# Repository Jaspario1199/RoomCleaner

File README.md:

# RoomCleaner 🧺🤖

An autonomous robot that scans your room, spots dirty laundry on the floor,
picks it up, and drops it in the hamper — using four winch motors in the
ceiling corners and a downward-facing gripper on cables.

> **▶ Interactive showcase:** [`showcase/index.html`](showcase/) — a live,
> self-contained portfolio page (browser simulation + engineering analysis +
> CAD). Open it in a browser or host it free on GitHub Pages.

> **Status:** Phase 0 complete + Phase 1 scaffolded. The kinematics, fan-aware
> motion planning, auto rest-pose, and the full scan→grab→deliver loop run today
> with **zero hardware**; a real open-vocabulary laundry detector runs on a
> webcam. You only need to fill in your room dimensions and ceiling-fan location.

---

## The idea in one picture

The machine is a **Cable-Driven Parallel Robot (CDPR)** — the same mechanism
that flies the "SkyCam" over a football stadium. Four motorized winches sit in
the ceiling corners; each pays out or reels in a cable. Where the cables meet is
the end-effector (the "claw"). Control the four cable lengths and you control the
claw's position anywhere in the room.

**Why a cable robot instead of arms or a rolling vacuum?**
- It reaches the *whole floor* from above — no bumping into furniture.
- The heavy motors stay bolted to the ceiling; only a light claw moves.
- The math (below) is clean and the parts are cheap.

The trade-off is the reachable area shrinks near the walls (cables can't pull the
claw sideways into a corner). Here's the safe workspace at a low height — green is
reachable, pink is not:

That pink border is a real design constraint: **laundry pushed right against a
wall is a hard case** we'll have to handle (e.g. a longer-reach end-effector, or
just accepting a small dead-zone).

### The ceiling fan is a hard no-go zone
If you have a ceiling fan, the robot's cables must **never** touch it. RoomCleaner
models the fan as a vertical keep-out cylinder and geometrically checks *every
cable* against it — a point is only reachable if all four cables clear the fan and
the claw stays out of it. The claw also **cruises below the fan** and **parks at
an auto-computed rest pose** out of the way between jobs. You just enter the fan's
center, blade radius, and how far it hangs down; the math does the rest. Good
news from the workspace map: laundry *under* the fan is still reachable, because
when the claw drops low the cables splay out to the corners and clear the blades.

---

## Quick start

```bash
pip install -r requirements.txt
python -m scripts.demo_sim       # 3D animation of a full cleaning run
python -m scripts.sim_tension_map  # heatmap: where the motors strain hardest
python -m scripts.sim_pickup_run   # per-pickup height / cable length / tension plots
python -m scripts.sim_payload_sweep         # max liftable weight, anywhere in the room
python -m scripts.sim_calibration_sensitivity # how precisely to measure your ceiling
python -m scripts.sim_workspace_volume      # 3D render of the reachable volume
python -m pytest                 # run the kinematics/geometry/vision tests

# Phase 1 — real laundry detection on a webcam (heavier deps):
pip install -r requirements-vision.txt
python -m scripts.detect_webcam                    # detect + print floor coordinates
python -m scripts.detect_and_plan --image floor.jpg  # full pipeline: detect -> localize -> PLAN
```

### The console (operator dashboard + live perception, one app)

A local single-page web app for watching and driving the robot from a browser:

```bash
pip install -r requirements-app.txt        # just Flask; core deps cover the rest
python -m roomcleaner.app --sim            # http://127.0.0.1:8000
# or:  python quickstart.py --app          # installs + launches in one step
python -m roomcleaner.app --live --camera 1  # real camera feed + detections
python -m roomcleaner.app --live --demo      # no camera: simulated laundry,
                                             # real detection→plan pipeline
```

It shows a live feed (MJPEG) with detection boxes and a sensitivity slider,
a detected-items panel with floor coordinates, status cards (phase, claw
position, items picked, claw link/battery), per-cable tension bars checked
against the 0.5–40 N motor band, a **Robot & plan** panel (nearest-first
pickup order + per-target cable lengths A–D + max tension + reachability), a
**3-D room view** with a Live view / Animate plan toggle, a scrolling
operations log, and operator controls: Start / Pause / Resume / STOP, Home,
Park, Grip/Release, a 0.1 m jog pad (workspace-clamped, fan keep-out
enforced), and a settings drawer for room/fan/hamper geometry. `--live` runs
the real camera through the validated capture+inference threads and wires the
serial winches + WiFi gripper only if they are reachable (otherwise
camera-only, motion disabled — bench-validate motion first). Details:
[`docs/APP.md`](docs/APP.md). The software STOP is not a safety device — the
physical kill switch remains the power strip.

`detect_and_plan` is the end-to-end brain: it takes a top-down photo (or
`--webcam 0`), detects the laundry, maps each item to a floor coordinate, runs
the real pickup planner, and saves an annotated image + a 3D scene. Test it on a
phone photo today — no camera or robot required.

The sim demo scatters fake laundry, then runs the real control loop to clear the
floor and animates the result. **Before anything else, open
`roomcleaner/config.py` and fill in the two "EDIT ME" blocks** — your room
dimensions and your ceiling-fan location/size.

---

## How it works (the four subsystems)

### 1. Kinematics — `roomcleaner/kinematics.py`
The core math, and it's simpler than it looks:

- **Inverse kinematics** ("put the claw *here* → how long is each cable?") is just
  the straight-line distance from each ceiling anchor to the target point.
- **Forward kinematics** ("cables are *these* lengths → where's the claw?") is a
  least-squares fit, because real cable measurements are never perfectly
  consistent.
- **Statics** ("can four *pull-only* cables actually hold the claw here without
  exceeding the motor's force limit?") defines the usable workspace. Cables can
  pull but never push, so this is the constraint that carves out those pink edges.

### 2. Perception — `roomcleaner/perception/`
Finds laundry and locates it on the floor. A `SimulatedDetector` invents laundry
for the sim, and `YoloWorldDetector` does the real thing on a webcam using an
**open-vocabulary** model (detects "sock", "towel", … from *words*, no training).
Both share the **exact same interface**, so the control loop never changes.
`localization.py` maps a camera pixel to a floor `(x, y)` — zero-calibration for a
straight-down ceiling camera, or a precise 4-point homography for a tilted one.
See **[docs/VISION.md](docs/VISION.md)**.

### 3. Motion planning — `roomcleaner/control/trajectory.py`
Turns "go to point X" into a smooth, ease-in/ease-out path. The `safe_transit`
helper always travels *up → across → down* so the claw never drags across the
floor or clips furniture.

### 4. Orchestration — `roomcleaner/control/state_machine.py`
The brain: an explicit state machine
(`SCAN → SELECT → APPROACH → GRAB → DELIVER → DONE`) that clears the floor one
item at a time, nearest first. Keeping it an explicit state machine (not tangled
`if`s) makes safety easy to reason about and new states easy to add.

---

## Repository layout

```
roomcleaner/
  config.py               # ROOM + FAN dimensions, motor limits, margins — the ONLY file you edit
  kinematics.py           # inverse/forward kinematics + statics/workspace + rest-pose finder
  geometry.py             # fan keep-out: exact cable-vs-cylinder intersection tests
  simulator.py            # 3D visualiser (renders to PNG/GIF, no display needed)
  perception/
    detector.py           # Detector interface + SimulatedDetector
    vision_detector.py    # real open-vocabulary laundry detector (YOLO-World)
    localization.py       # pixel → floor (x,y): overhead-linear + homography mappers
    camera.py             # webcam capture wrapper (OpenCV)
  control/
    trajectory.py         # smooth path generation
    state_machine.py      # the scan→grab→deliver brain (emits move/grip/release actions)
  hardware/
    driver.py             # positions → winch steps + serial protocol (Serial/Mock)
    gripper.py            # gripper backends: WiFiGripper (wireless claw) / Serial / Mock
    executor.py           # stream a plan to the motors + gripper
    hw_config.py          # steps/rev, microstepping, drum dia, serial port, effector IP
roomcleaner/cdpr/         # GEN-2 CONTROL SYSTEM (see docs/CONTROL_SYSTEM_V1.md)
  station_core.py         # executable spec of the winch-station firmware
  coordinator.py          # synchronized segment streams, feed-hold, leases
  calibration.py          # self-calibration estimator + identifiability + excitation
  startup.py              # DISARMED -> ... -> READY sequencer (bounded, abortable)
  homing.py               # sequential bead verification
  supervisor.py           # PAUSED/FAULT/RECOVERY_REQUIRED/PARKED, no auto-resume
  tasks.py                # SCAN -> ... -> DELIVERY_VERIFICATION
  service.py, static/     # phone setup page + API (python -m roomcleaner.cdpr.service --sim)
  sim/                    # physics world, simulated stations/network/camera/claw
firmware/
  winch_station/          # gen-2 station core (C++, conformance-tested vs Python)
  claw_s3/                # gen-2 claw node: camera frames, IMU, servo, battery
  roomcleaner_firmware/   # Arduino sketch: 4 winch steppers + homing (wired)
  effector_esp32/         # ESP32 sketch: wireless gripper servo over WiFi
scripts/
  demo_sim.py             # end-to-end simulation demo
  detect_webcam.py        # live laundry detection from a webcam
  detect_and_plan.py      # full pipeline: image/webcam → detect → localize → plan
  hardware_dryrun.py      # print the serial command stream (no Arduino needed)
tests/
  test_kinematics.py      # the math we must trust
  test_geometry.py        # fan keep-out safety tests
  test_localization.py    # pixel → floor mapping tests
docs/
  ROADMAP.md              # phase-by-phase build plan
  HARDWARE.md             # BOM (cheap Amazon parts) + gripper recommendation
  VISION.md               # perception & camera calibration guide
  ARCHITECTURE.md         # how the pieces fit + the design decisions
  RESEARCH.md             # sources behind the hardware/gripper choices
```

---

## Where this is going

See **[docs/ROADMAP.md](docs/ROADMAP.md)** for the full plan. The short version:

| Phase | What | Cost |
|------|------|------|
| **0** ✅ | Kinematics + simulator + control loop + fan safety + rest pose | Free (software) |
| **1** 🚧 | Real laundry detection & floor localization (runs on a webcam) | Free–cheap (a webcam) |
| **2** | Motion planning polish, full-path safety, sim tuning | Free |
| **3** | Hardware bring-up: motors, drivers, camera, e-stop | 💰 the build (~$250–515, see BOM) |
| **4** | The grasp — actually picking cloth off the floor | 💰 the experiment |

The two genuinely hard, risky parts are called out honestly in the docs:
**grasping deformable cloth** (Phase 4) and **safety** (a motor that can move a
payload across your ceiling can hurt someone). We de-risk everything cheap in
software first.

---

## The gripper — a tentacle hand (mechanical, no vacuum)

Grabbing crumpled cloth off a hard floor is the classic failure point. The chosen
design is a **ring of tendon-driven curling "tentacle" fingers** that descend and
curl **inward and under**, raking and wrapping the laundry toward the center — one
servo closes them all. For real, crumpled laundry this beats a rigid claw because
it gathers rather than needing something to pinch. It's fully modeled and
print-ready in **[`cad/`](cad/)** (`tentacle_finger` × 5 + `tentacle_hub` +
`effector_frame`). Full reasoning and the needle-gripper fallback are in
**[docs/HARDWARE.md](docs/HARDWARE.md)**.

## 3D-printed parts (CAD)

Everything mechanical that can be printed is provided as **parametric CadQuery
scripts** exporting genuine **STEP** + **STL** files: winch spools, motor mounts,
corner guides, the end-effector frame, and the whole tentacle gripper. Edit your
dimensions in `cad/params.py` and run `python -m cad.export_all` to regenerate.
See **[cad/README.md](cad/README.md)** for print settings and assembly. (The
load-bearing ceiling anchors stay **metal** — never printed.)

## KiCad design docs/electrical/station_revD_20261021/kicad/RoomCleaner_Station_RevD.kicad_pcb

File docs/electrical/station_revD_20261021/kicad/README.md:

# Winch station Rev D, as soldered: KiCad 7 project

One A3 schematic, a netlist, a PDF/PNG, and a no-routing PCB (ratsnest only) of the
station perfboard (5 x 7 cm, 24 columns A-X x 18 rows 01-18, 2.54 mm). Everything is
generated from `../perfboard_layout.py`, the as-soldered, net-checked design. If the
Rev D schematic (`../draw_schematic.py`, `../README.md`) and the perfboard file disagree,
the perfboard file wins (list below). Current limit: DECISIONS.md **D30** (Vref about
0.85 V, about 1.06 A), not the 1.35 A / 1.08 V of the Rev D README.

## Open it

KiCad 7.0.x: open `RoomCleaner_Station_RevD.kicad_pro`.
The schematic is `RoomCleaner_Station_RevD.kicad_sch` (A3, one sheet), the PCB
`RoomCleaner_Station_RevD.kicad_pcb`. `sym-lib-table` / `fp-lib-table` name the stock
libraries through `${KICAD7_SYMBOL_DIR}` / `${KICAD7_FOOTPRINT_DIR}` and the project
libraries `RoomCleaner.kicad_sym` / `RoomCleaner.pretty` through `${KIPRJMOD}`.
The PCB shows the connections as a ratsnest (no tracks: the copper on the real board is
bare wire and solder runs, see `../PERFBOARD_LAYOUT.md`).

| File | What |
|---|---|
| `build_kicad.py` | generator for everything below (also runs the exports, the PCB, DRC, the net check) |
| `perfboard_data.py` | the bridge to `perfboard_layout.py`: loads its tables, holds the one hole-to-pin map |
| `check_netlist.py` | compares the exported netlist (and the PCB) with the perfboard nets; prints PASS/FAIL |
| `run_erc_xvfb.py` | runs KiCad's real ERC headlessly (see ERC below) |
| `RoomCleaner_Station_RevD.kicad_pro/.kicad_sch/.kicad_pcb` | project, schematic, PCB |
| `RoomCleaner.kicad_sym`, `RoomCleaner.pretty/` | custom XIAO ESP32-C3 and DROK buck symbols + footprints |
| `sym-lib-table`, `fp-lib-table` | project library tables |
| `RoomCleaner_Station_RevD_netlist.xml` | `kicad-cli sch export netlist --format kicadxml` |
| `RoomCleaner_Station_RevD.pdf`, `..._preview.png` | `kicad-cli sch export pdf`, `pdftoppm -r 110 -png` |
| `netlist_check.txt` | output of `check_netlist.py --pcb` (PASS) |
| `RoomCleaner_Station_RevD_erc.rpt` | KiCad 7 ERC report (0 errors, 0 warnings) |
| `RoomCleaner_Station_RevD_drc.rpt`, `..._pcb_preview.png` | PCB DRC report; trimmed render of the placed board |

## Regenerate

```
cd docs/electrical/station_revD_20261021/kicad
/usr/bin/python3 build_kicad.py            # project, netlist, PDF, PNG, PCB, DRC, netlist_check.txt
/usr/bin/python3 build_kicad.py --erc      # same + real ERC through eeschema under Xvfb (about 1 min)
/usr/bin/python3 build_kicad.py --no-pcb   # schematic side only (also --no-export, --no-drc)
python3 check_netlist.py                   # netlist only, stdlib only; add --pcb with /usr/bin/python3
```

Use `/usr/bin/python3` (the one with `pcbnew`). `perfboard_layout.py` is **not imported**:
importing it runs its matplotlib code and rewrites `perfboard_layout.png/.pdf`. Instead
`perfboard_data.py` executes only its table/check section (above the `# --- drawing`
marker) and never writes anything outside this folder. Schematic, libraries and project
files are deterministic (fixed UUID namespace); the netlist XML carries a date and pcbnew
assigns fresh item UUIDs to the PCB on every run.

Where a perfboard fact had to be turned into a schematic fact, the map lives in one place,
`perfboard_data.py`: `HOLE_PIN` (hole -> connector/part pin, with the perfboard label as a
cross-check), `XIAO_PIN`, `A4988_PIN` + `A4988_GND_BY_HOLE`, and `NET_NAME`
(perfboard `12V`/`3V3`/`5V` -> the power symbols `+12V`/`+3V3`/`+5V`; `PGND` is folded into
`GND` by the perfboard file's own `NETMAP`). Every hole in `PINS` must be mapped exactly once,
and the generator checks that the XIAO / A4988 pin names match the perfboard labels. The PCB
step then places each footprint with pad 1 on its hole and checks that **every pad of every
footprint lands on the hole the map says** (worst error 0.04 mm, C1), which independently
confirms the pad numbering of the stock A4988 footprint.

## Results

* **ERC (KiCad 7.0.11): 0 errors, 0 warnings.** Note: `kicad-cli` 7.0.11 has **no**
  `sch erc` (or `pcb drc`) subcommand; both arrived in KiCad 8. The ERC was therefore run with
  the real eeschema ERC engine by driving the GUI under Xvfb (`run_erc_xvfb.py`: Inspect >
  Electrical Rules Checker > Run ERC > Save, on a temporary copy of the project and a temporary
  config dir). KiCad's only ignored test is its default-off "SPICE model issue". To show the run
  is not vacuous, the same script on a copy with the three PWR_FLAGs and one wire removed
  reports 4 errors (pin not connected, 3x power pin not driven). PWR_FLAGs: +12V and GND at J1,
  +5V at JP1's XIAO side. The stock-symbol copies embedded in the schematic match the library
  (no "symbol doesn't match library" warning).
* **Netlist: PASS** (`netlist_check.txt`): 16 nets / 55 connected pins identical, per net, to the
  perfboard; 6 pins unconnected on both sides (U1 EN, XIAO D0 D6 D7 D8 D9); 14 components.
  Mutation tests (a pin dropped from SDA, a pin moved from STEP to EN) print FAIL.
* **PCB / DRC:** 70 x 50 mm outline, hole A01 at (101.6, 76.2) mm with equal margins to the
  board edge (5.79 / 3.41 mm), all 14 footprints on their holes, 22 nets (16 + 6 `unconnected-`),
  no routing. DRC runs through `pcbnew.WriteDRCReport` (same engine as the GUI): **0 errors
  other than the 39 "unconnected items" (the ratsnest)**, 5 warnings: 3 courtyard overlaps on
  adjacent holes (JP1/D1, JP1/U3, R4/J3; the bodies do not collide, the stock 0.5 mm connector
  courtyard margins do) which the project sets to *warning* (`courtyards_overlap` in
  `.kicad_pro`), and 2 silkscreen overlaps between neighbouring outlines around JP1 / U3 (x 142-146 mm). Designators are on the
  fab layer to keep the silk readable. Footprints carry the schematic symbol UUID path so
  "Update PCB from Schematic" should match them (not exercised in the GUI).

## What is off-board

Drawn as dashed blocks next to their connectors, not as parts: **AS5600 encoder** on J5
(C17-F17: 3V3, GND, SDA, SCL), **KW12-3 NC switch** on J3 (H17 NC -> HOME, I17 COM -> GND),
the **NEMA 17 motor** on J2 (X05-X08), the **12 V supply branch** on J1 (+ its supply-end fuses
F0-F4, which are notes only) and the XIAO's USB cable. The DROK module is modeled as a 5-pin
header part (pads only; its body is not modeled).

## Disagreements Rev D schematic vs perfboard (perfboard followed)

1. Current limit: Rev D README / sheet 3 / sheet 5 say 1.35 A, Vref 1.08 V (D29). The sheet
   follows D30: **Vref 0.85 V, about 1.06 A**; 1.08 V is noted as not reachable on this carrier.
2. Encoder: sheet 3 draws AS5600 DIR -> GND and OUT open at the encoder. The perfboard J5 has
   4 pins only (3V3, GND, SDA, SCL), so those two connections are on the encoder board, not
   the perfboard.
3. Test points TP0-TP4 (sheets 1, 2, 4) are not parts on the perfboard; omitted.
4. Grounds: Rev D shows one GND. The perfboard has two A4988 GND pads (pad 7 next to VMOT =
   motor return `PGND`, pad 1 = logic) joined by wire S03-O11; after `NETMAP` that is one net,
   drawn as one `GND`.
5. Net names: Rev D sheet 4 (`+12_STATION`, `+5_BUCK`, `DIODE OUTPUT`, `XIAO_5V`, `ENABLE`,
   `HOME_NC`) are `+12V`, `5VB`, `5VD`, `+5V`, `EN`, `HOME` here.
6. Packages as built: R2/R3 stand upright (2.54 mm holes), R1/R4 lie (7.62 mm); J1 uses a
   5.08 mm terminal pitch (X01 / X03), not a 2.54 mm header.

## Known limits

* Footprints: stock footprints except the XIAO (outline approximate) and the DROK header.
  R = DIN0204 (3.6 mm) so the 2.54 mm-pitch courtyards of R1-R3 do not collide; any 1/8-1/4 W
  10k fits electrically. C1 = `CP_Radial_D6.3mm_P2.50mm` (2.50 vs 2.54 mm hole pitch, 0.04 mm
  off); the real 100 uF/50 V can may be larger. J1 uses the 5.08 mm terminal footprint instead
  of a pin header because X01-X03 are 5.08 mm apart. No 3D models for the custom footprints.
* Resistors and JP1 are symmetric; their pin 1/2 assignment is arbitrary (pin 1 = upper lead in
  the drawing, JP1 pin 1 = diode side).
* The schematic is a connectivity drawing of the soldered board. ERC and the net check prove it
  matches `perfboard_layout.py`; they do not prove `perfboard_layout.py` matches the hardware
  (meter-check the board, see the power-up note on the sheet). The DROK revision is unverified.
* The PCB is a placement / ratsnest aid for the perfboard, not a fabrication board (no tracks,
  no mounting holes, no copper). 3 courtyard overlaps are downgraded to warnings on purpose.
* `run_erc_xvfb.py` is coordinate-based (tested on KiCad 7.0.11, Xvfb 1600x1000, fresh config)
  and needs `Xvfb`, `eeschema`, `libX11`, `libXtst`. With KiCad 8+ use `kicad-cli sch erc`.

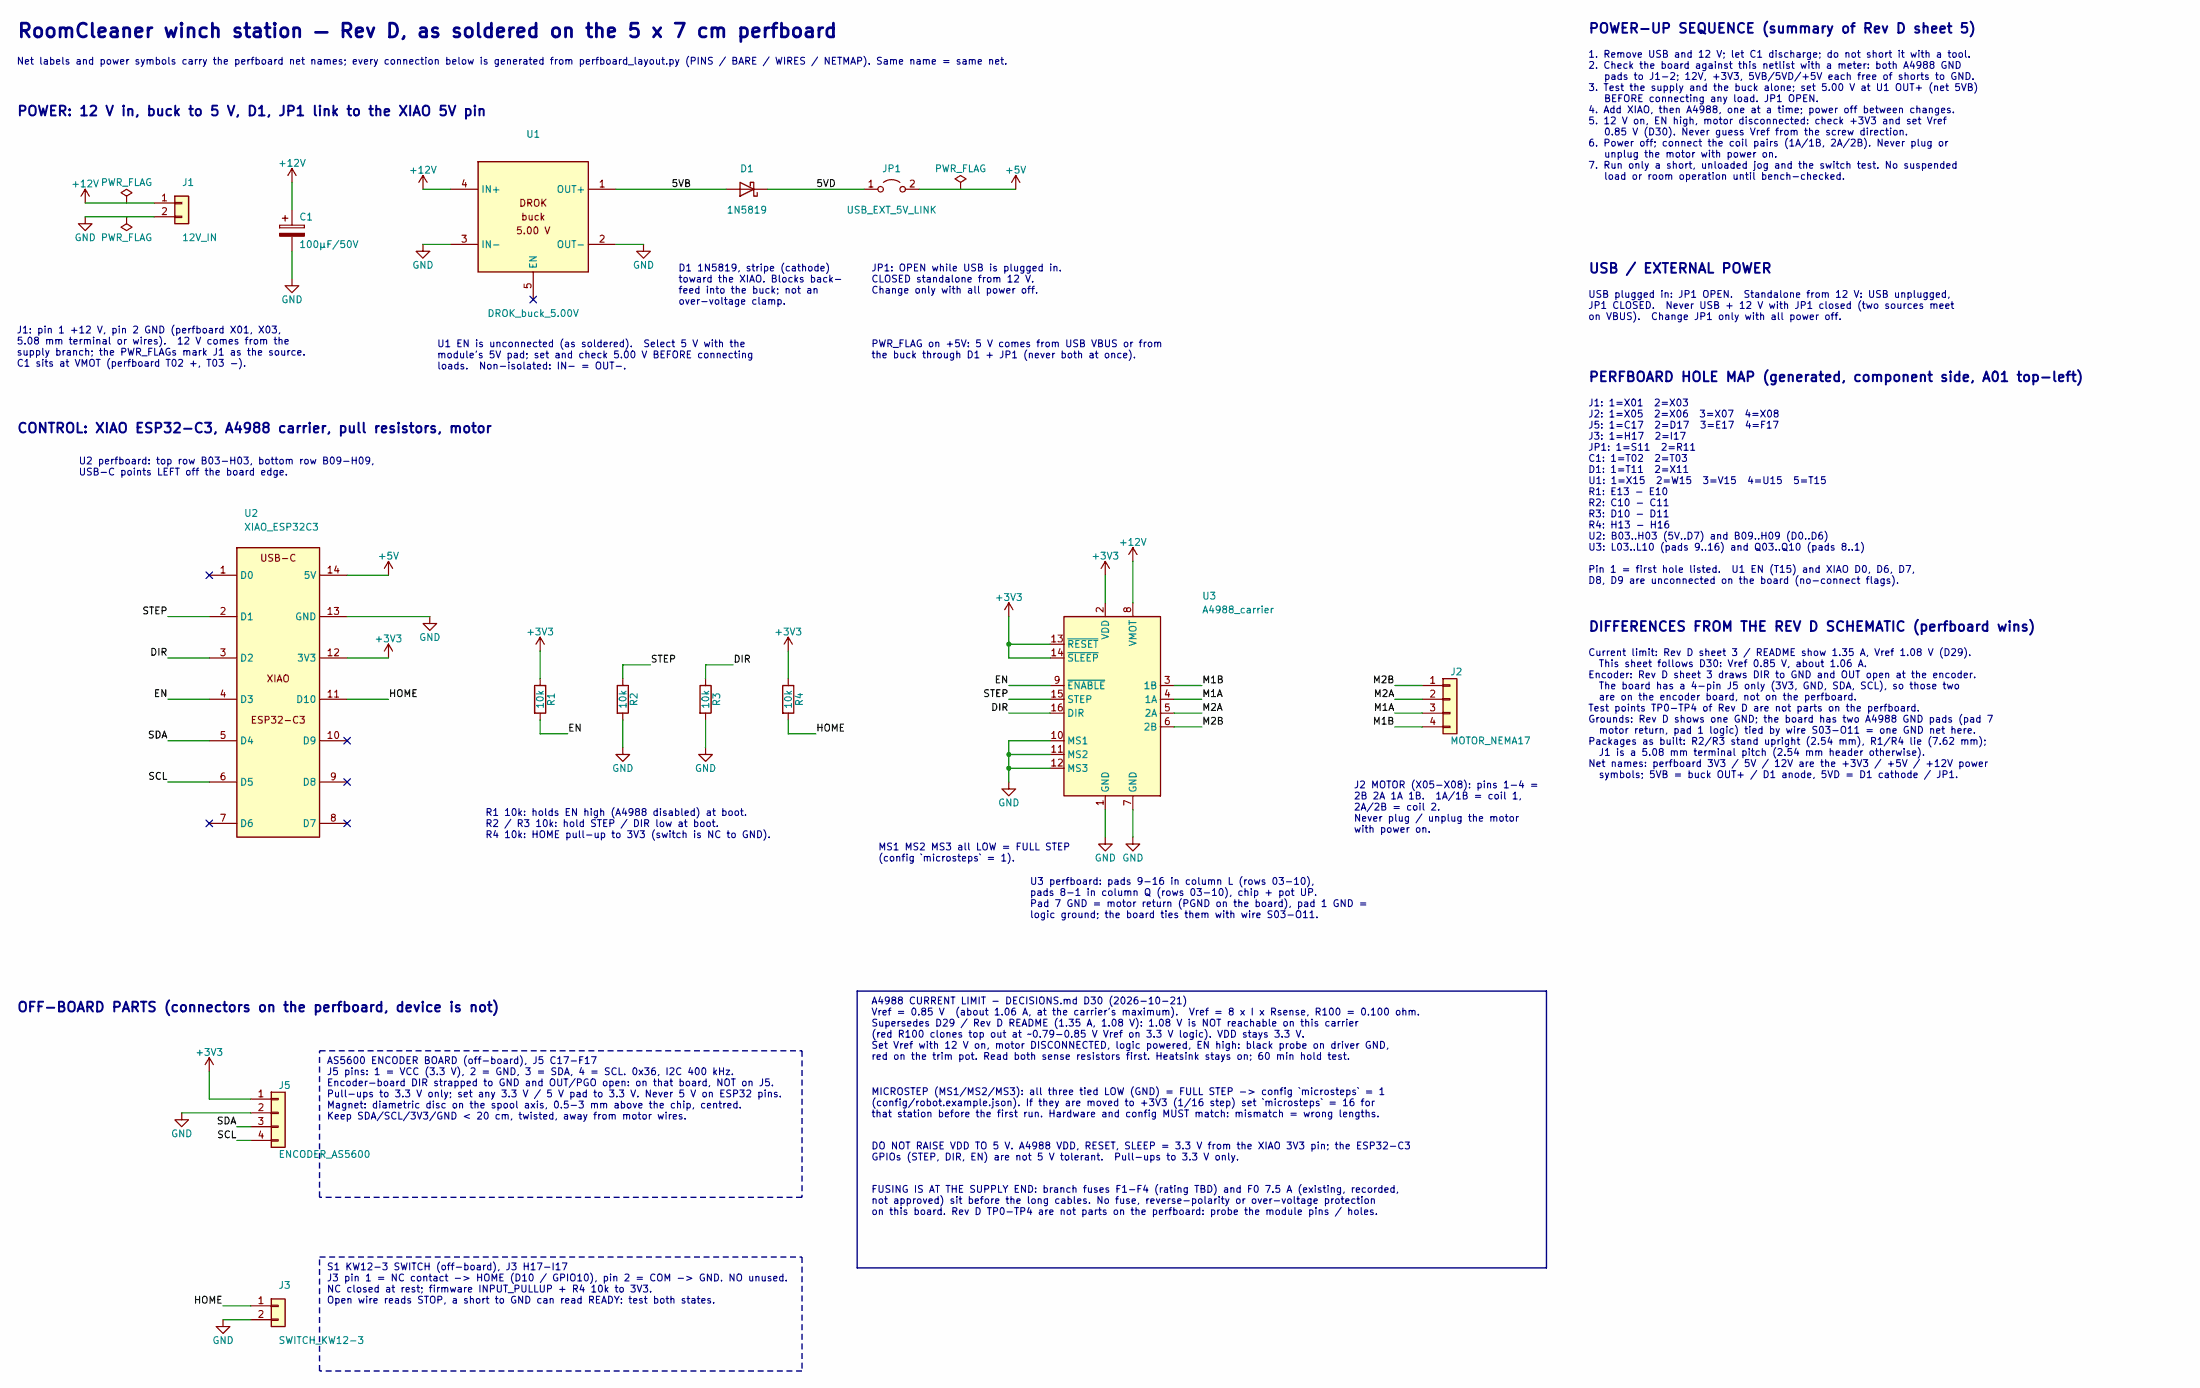
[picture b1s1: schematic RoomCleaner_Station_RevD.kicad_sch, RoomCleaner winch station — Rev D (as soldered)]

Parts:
C1: 100µF/50V; CP_Radial_D6.3mm_P2.50mm
D1: 1N5819; D_DO-41_SOD81_P10.16mm_Horizontal
J1: 12V_IN; TerminalBlock_bornier-2_P5.08mm
J2: MOTOR_NEMA17; PinHeader_1x04_P2.54mm_Vertical
J3: SWITCH_KW12-3; PinHeader_1x02_P2.54mm_Vertical
J5: ENCODER_AS5600; PinHeader_1x04_P2.54mm_Vertical
JP1: USB_EXT_5V_LINK; PinHeader_1x02_P2.54mm_Vertical
R1, R4: 10k; R_Axial_DIN0204_L3.6mm_D1.6mm_P7.62mm_Horizontal
R2, R3: 10k; R_Axial_DIN0204_L3.6mm_D1.6mm_P2.54mm_Vertical
U1: DROK_buck_5.00V; DROK_Buck_5pin_Header
U2: XIAO_ESP32C3; XIAO_ESP32C3_THT
U3: A4988_carrier; Pololu_Breakout-16_15.2x20.3mm

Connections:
+3V3: J5.1, R1.1, R4.1, U2.12 (3V3), U3.2 (VDD), U3.13 (~RESET), U3.14 (~SLEEP)
+5V: JP1.2 (B), U2.14 (5V)
+12V: C1.1, J1.1, U1.4 (IN+), U3.8 (VMOT)
/5VB: D1.2 (A), U1.1 (OUT+)
/5VD: D1.1 (K), JP1.1 (A)
/DIR: R3.1, U2.3 (D2), U3.16 (DIR)
/EN: R1.2, U2.4 (D3), U3.9 (~ENABLE)
/HOME: J3.1, R4.2, U2.11 (D10)
/M1A: J2.3, U3.4 (1A)
/M1B: J2.4, U3.3 (1B)
/M2A: J2.2, U3.5 (2A)
/M2B: J2.1, U3.6 (2B)
/SCL: J5.4, U2.6 (D5)
/SDA: J5.3, U2.5 (D4)
/STEP: R2.1, U2.2 (D1), U3.15 (STEP)
GND: C1.2, J1.2, J3.2, J5.2, R2.2, R3.2, U1.2 (OUT-), U1.3 (IN-), U2.13 (GND), U3.1 (GND), U3.7 (GND), U3.10 (MS1), U3.11 (MS2), U3.12 (MS3)

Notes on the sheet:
RoomCleaner winch station — Rev D, as soldered on the 5 x 7 cm perfboard
Net labels and power symbols carry the perfboard net names; every connection below is generated from perfboard_layout.py (PINS / BARE / WIRES / NETMAP). Same name = same net.
POWER: 12 V in, buck to 5 V, D1, JP1 link to the XIAO 5V pin
J1: pin 1 +12 V, pin 2 GND (perfboard X01, X03, 5.08 mm terminal or wires). 12 V comes from the supply branch; the PWR_FLAGs mark J1 as the source. C1 sits at VMOT (perfboard T02 +, T03 -).
U1 EN is unconnected (as soldered). Select 5 V with the module's 5V pad; set and check 5.00 V BEFORE connecting loads. Non-isolated: IN- = OUT-.
D1 1N5819, stripe (cathode) toward the XIAO. Blocks back- feed into the buck; not an over-voltage clamp.
JP1: OPEN while USB is plugged in. CLOSED standalone from 12 V. Change only with all power off.
PWR_FLAG on +5V: 5 V comes from USB VBUS or from the buck through D1 + JP1 (never both at once).
CONTROL: XIAO ESP32-C3, A4988 carrier, pull resistors, motor
U2 perfboard: top row B03-H03, bottom row B09-H09, USB-C points LEFT off the board edge.
R1 10k: holds EN high (A4988 disabled) at boot. R2 / R3 10k: hold STEP / DIR low at boot. R4 10k: HOME pull-up to 3V3 (switch is NC to GND).
MS1 MS2 MS3 all LOW = FULL STEP (config `microsteps` = 1).
U3 perfboard: pads 9-16 in column L (rows 03-10), pads 8-1 in column Q (rows 03-10), chip + pot UP. Pad 7 GND = motor return (PGND on the board), pad 1 GND = logic ground; the board ties them with wire S03-O11.
J2 MOTOR (X05-X08): pins 1-4 = 2B 2A 1A 1B. 1A/1B = coil 1, 2A/2B = coil 2. Never plug / unplug the motor with power on.
OFF-BOARD PARTS (connectors on the perfboard, device is not)
AS5600 ENCODER BOARD (off-board), J5 C17-F17 J5 pins: 1 = VCC (3.3 V), 2 = GND, 3 = SDA, 4 = SCL. 0x36, I2C 400 kHz. Encoder-board DIR strapped to GND and OUT/PGO open: on that board, NOT on J5. Pull-ups to 3.3 V only; set any 3.3 V / 5 V pad to 3.3 V. Never 5 V on ESP32 pins. Magnet: diametric dis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
S1 KW12-3 SWITCH (off-board), J3 H17-I17 J3 pin 1 = NC contact -> HOME (D10 / GPIO10), pin 2 = COM -> GND. NO unused. NC closed at rest; firmware INPUT_PULLUP + R4 10k to 3V3. Open wire reads STOP, a short to GND can read READY: test both states.
A4988 CURRENT LIMIT - DECISIONS.md D30 (2026-10-21) Vref = 0.85 V (about 1.06 A, at the carrier's maximum). Vref = 8 x I x Rsense, R100 = 0.100 ohm. Supersedes D29 / Rev D README (1.35 A, 1.08 V): 1.08 V is NOT reachable on this carrier (red R100 clones top out at ~0.79-0.85 V Vref on 3.3 V logic).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
MICROSTEP (MS1/MS2/MS3): all three tied LOW (GND) = FULL STEP -> config `microsteps` = 1 (config/robot.example.json). If they are moved to +3V3 (1/16 step) set `microsteps` = 16 for that station before the first run. Hardware and config MUST match: mismatch = wrong lengths.
DO NOT RAISE VDD TO 5 V. A4988 VDD, RESET, SLEEP = 3.3 V from the XIAO 3V3 pin; the ESP32-C3 GPIOs (STEP, DIR, EN) are not 5 V tolerant. Pull-ups to 3.3 V only.
FUSING IS AT THE SUPPLY END: branch fuses F1-F4 (rating TBD) and F0 7.5 A (existing, recorded, not approved) sit before the long cables. No fuse, reverse-polarity or over-voltage protection on this board. Rev D TP0-TP4 are not parts on the perfboard: probe the module pins / holes.
POWER-UP SEQUENCE (summary of Rev D sheet 5)
1. Remove USB and 12 V; let C1 discharge; do not short it with a tool. 2. Check the board against this netlist with a meter: both A4988 GND pads to J1-2; 12V, +3V3, 5VB/5VD/+5V each free of shorts to GND. 3. Test the supply and the buck alone; set 5.00 V at U1 OUT+ (net 5VB) BEFORE connecting any l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
USB / EXTERNAL POWER
USB plugged in: JP1 OPEN. Standalone from 12 V: USB unplugged, JP1 CLOSED. Never USB + 12 V with JP1 closed (two sources meet on VBUS). Change JP1 only with all power off.
PERFBOARD HOLE MAP (generated, component side, A01 top-left)
J1: 1=X01 2=X03 J2: 1=X05 2=X06 3=X07 4=X08 J5: 1=C17 2=D17 3=E17 4=F17 J3: 1=H17 2=I17 JP1: 1=S11 2=R11 C1: 1=T02 2=T03 D1: 1=T11 2=X11 U1: 1=X15 2=W15 3=V15 4=U15 5=T15 R1: E13 - E10 R2: C10 - C11 R3: D10 - D11 R4: H13 - H16 U2: B03..H03 (5V..D7) and B09..H09 (D0..D6) U3: L03..L10 (pads 9..16) an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
DIFFERENCES FROM THE REV D SCHEMATIC (perfboard wins)
Current limit: Rev D sheet 3 / README show 1.35 A, Vref 1.08 V (D29). This sheet follows D30: Vref 0.85 V, about 1.06 A. Encoder: Rev D sheet 3 draws DIR to GND and OUT open at the encoder. The board has a 4-pin J5 only (3V3, GND, SDA, SCL), so those two are on the encoder board, not on the perfboa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

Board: 2 copper layers, 14 parts (0 on the bottom side), 16 nets, no tracks yet.

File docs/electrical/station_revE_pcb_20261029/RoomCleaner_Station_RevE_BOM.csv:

Process,Reference,Qty/board,Qty/10 boards,Value,Description,Footprint,Manufacturer part,Supplier / note
"machine placed (SMD, top, reflow)",D1,1,10,SS14,"Schottky 40 V 1 A, SMA (replaces 1N5819 DO-41, same function)",Diode_SMD:D_SMA,onsemi SS14 / MDD SS14,LCSC C2480 (verify before ordering)
"machine placed (SMD, top, reflow)",R1 R2 R3 R4,4,40,10k,"10k 1% 1/4 W thick film, 1206",Resistor_SMD:R_1206_3216Metric,Yageo RC1206FR-0710KL,LCSC C17902 (verify before ordering)
"hand soldered (THT, after reflow)",C1,1,10,100uF 50V,"100 uF 50 V aluminium electrolytic, radial 8 mm, 3.5 mm pitch",RoomCleanerRevE:CP_Radial_D8.0mm_P3.50mm_BigPad,Panasonic EEU-FR1H101,
"hand soldered (THT, after reflow)",J1,1,10,12V IN,Screw terminal 2-pole 5.08 mm,"RoomCleanerRevE:TerminalBlock_Phoenix_MKDS-1,5-2-5.08_1x02_P5.08mm_Horizontal_BigPad","Phoenix Contact 1729128 (MKDS 1,5/ 2-5,08)",
"hand soldered (THT, after reflow)",J2,1,10,MOTOR,"JST-XH 4-pin, top entry",RoomCleanerRevE:JST_XH_B4B-XH-A_1x04_P2.50mm_Vertical_BigPad,JST B4B-XH-A(LF)(SN),mating XHP-4 + SXH-001T-P0.6 crimps
"hand soldered (THT, after reflow)",J3,1,10,SWITCH,"JST-XH 2-pin, top entry",RoomCleanerRevE:JST_XH_B2B-XH-A_1x02_P2.50mm_Vertical_BigPad,JST B2B-XH-A(LF)(SN),mating XHP-2 + SXH-001T-P0.6 crimps
"hand soldered (THT, after reflow)",J5,1,10,ENCODER,"JST-XH 4-pin, top entry",RoomCleanerRevE:JST_XH_B4B-XH-A_1x04_P2.50mm_Vertical_BigPad,JST B4B-XH-A(LF)(SN),mating XHP-4 + SXH-001T-P0.6 crimps
"hand soldered (THT, after reflow)",JP1,1,10,USB/EXT 5V link,1x2 male header 2.54 mm + jumper shunt,RoomCleanerRevE:PinHeader_1x02_P2.54mm_Vertical_BigPad,Sullins PRPC002SAAN-RC + QPC02SXGN-RC,
"hand soldered (THT, after reflow)",U1,1,10,DROK buck 5.00V,"Socket: 1x5 female header 2.54 mm (module: DROK mini buck, set to 5.00 V)",RoomCleanerRevE:DROK_Buck_Socket_1x5,Sullins PPTC051LFBN-RC,
"hand soldered (THT, after reflow)",U2,2,20,XIAO ESP32-C3,"Socket: 2 x 1x7 female header 2.54 mm (module: Seeed XIAO ESP32-C3, 113991054)",RoomCleanerRevE:XIAO_ESP32C3_Socket_2x7,Sullins PPTC071LFBN-RC,2 strips per board
"hand soldered (THT, after reflow)",U3,2,20,A4988 carrier,"Socket: 2 x 1x8 female header 2.54 mm (module: Pololu A4988 carrier, #1182)",RoomCleanerRevE:Pololu_A4988_Socket_2x8,Sullins PPTC081LFBN-RC,2 strips per board
not a part,TP1 TP2 TP3 TP4,4,40,test pads,bare plated pads,,,
not a part,FID1 FID2 FID3,3,30,fiducials,"1 mm copper, 2 mm mask opening",,,
not a part,H1 H2 H3 H4,4,40,M3 holes,3.2 mm unplated,,,
modules (plug in),U1 U2 U3,1 each,10 each,"DROK buck, XIAO ESP32-C3, A4988 carrier","plugged into the sockets, not soldered to this board",,,

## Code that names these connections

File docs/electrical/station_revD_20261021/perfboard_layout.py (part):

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    pin(f"Q{r:02d}", net, lab)
# connectors
pin("X01", "12V", "+12"); pin("X03", "PGND", "GND")                         # J1 power in
for r, n in zip((5, 6, 7, 8), ("M2B", "M2A", "M1A", "M1B")): pin(f"X{r:02d}", n, n[1:])   # J2 motor
pin("C17", "3V3", "3V3"); pin("D17", "GND", "GND"); pin("E17", "SDA", "SDA"); pin("F17", "SCL", "SCL")  # J5 encoder
pin("H17", "HOME", "NC"); pin("I17", "GND", "COM")                           # J3 switch
# U1 DROK buck: 5-pin single-row header (OUT+, OUT-, IN-, IN+, EN), standing upright in row 15
pin("X15", "5VB", "OUT+"); pin("W15", "PGND", "OUT-"); pin("V15", "PGND", "IN-"); pin("U15", "12V", "IN+")
pin("T15", "nc", "EN")
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pin("C10", "STEP", "R2"); pin("C11", "GND", "R2")                            # R2 STEP pull-down
pin("D10", "DIR", "R3"); pin("D11", "GND", "R3")                             # R3 DIR pull-down
pin("E10", "EN", "R1"); pin("E13", "3V3", "R1")                              # R1 EN pull-up
pin("H16", "HOME", "R4"); pin("H13", "3V3", "R4")                            # R4 HOME pull-up

# ---------------- bare runs (bottom side) and insulated wires
BARE = []
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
